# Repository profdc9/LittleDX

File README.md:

# LittleDX

New super cheap all-mode transceiver, details to come.

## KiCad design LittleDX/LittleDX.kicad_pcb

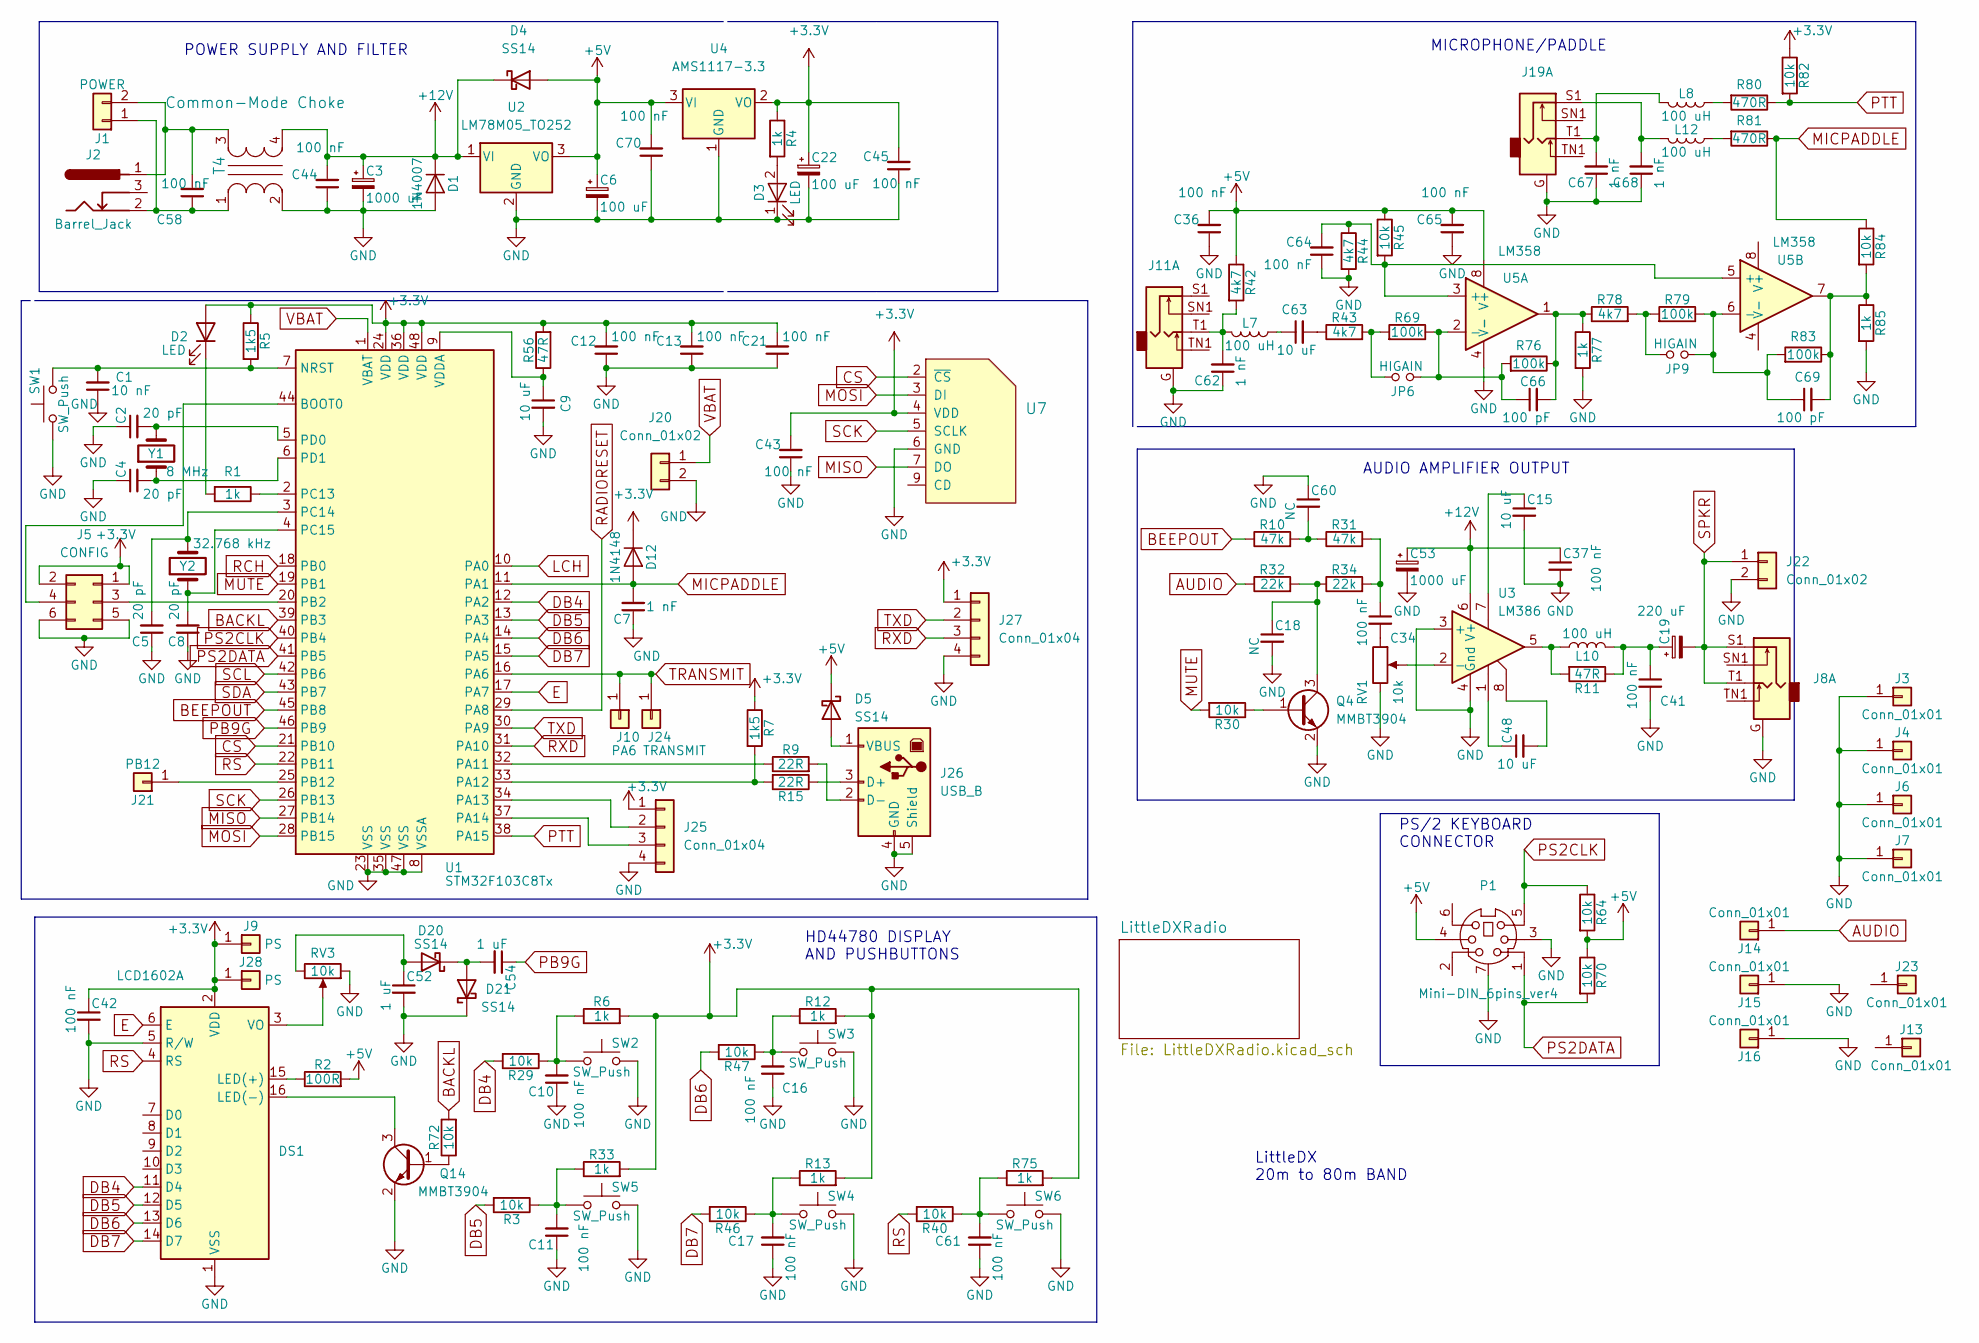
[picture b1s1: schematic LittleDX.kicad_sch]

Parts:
C1: 10 nF; C_0805_2012Metric_Pad1.18x1.45mm_HandSolder; LCSC C1710
C2, C4, C5, C8: 20 pF; C_0805_2012Metric_Pad1.18x1.45mm_HandSolder; LCSC C1804
C3, C53: 1000 uF; CP_Radial_D8.0mm_P3.50mm
C6: 100 uF; CP_Radial_D5.0mm_P2.50mm
C7, C62, C67, C68: 1 nF; C_0805_2012Metric_Pad1.18x1.45mm_HandSolder; LCSC C46653
C9, C15, C48, C63: 10 uF; C_0805_2012Metric_Pad1.18x1.45mm_HandSolder; LCSC C15850
C10, C11, C12, C13, C16, C17, C21, C36, C37, C41, C42, C43, C44, C45, C58, C61, C64, C65, C70: 100 nF; C_0805_2012Metric_Pad1.18x1.45mm_HandSolder; LCSC C49678
C18, C60: NC; C_0805_2012Metric_Pad1.18x1.45mm_HandSolder
C19: 220 uF; CP_Radial_D7.5mm_P2.50mm
C22: 100 uF; CP_Radial_D5.0mm_P2.00mm
C34: 100 nF; C_0805_2012Metric_Pad1.18x1.45mm_HandSolder
C52, C54: 1 uF; C_0805_2012Metric_Pad1.18x1.45mm_HandSolder; LCSC C28323
C66, C69: 100 pF; C_0805_2012Metric_Pad1.18x1.45mm_HandSolder; LCSC C1790
D1: 1N4007; D_DO-41_SOD81_P7.62mm_Horizontal
D2, D3: LED; LED_0805_2012Metric_Pad1.15x1.40mm_HandSolder; LCSC C2296
D4, D5, D20, D21: SS14; D_SMA_Handsoldering; LCSC C2480
D12: 1N4148; D_SOD-123; LCSC C81598
DS1: LCD1602A; WC1602A
J1: POWER; TerminalBlock_bornier-2_P5.08mm
J2: Barrel_Jack; BARREL_JACK
J3, J4, J6, J7, J13: Conn_01x01; 1pin
J5: CONFIG; PinHeader_2x03_P2.54mm_Vertical
J8, J11, J19: AudioJack2_Dual_Ground_Switch; PJ-3240-35mm-stereo
J9, J28: PS; PinHeader_1x01_P2.54mm_Vertical
J10: PA6; PinHeader_1x01_P2.54mm_Vertical
J14, J15, J16: Conn_01x01; Pin_Header_Straight_1x01_Pitch2.54mm
J20, J22: Conn_01x02; PinHeader_1x02_P2.54mm_Vertical
J21: PB12; PinHeader_1x01_P2.54mm_Vertical
J23: Conn_01x01; MountingHole_3.2mm_M3
J24: TRANSMIT; PinHeader_1x01_P2.54mm_Vertical
J25, J27: Conn_01x04; PinHeader_1x04_P2.54mm_Vertical
J26: USB_B; USB_B_OST_USB-B1HSxx_Horizontal
JP6, JP9: HIGAIN; PinHeader_1x02_P2.54mm_Vertical
L7, L8, L12: 100 uH; L_0805_2012Metric_Pad1.15x1.40mm_HandSolder; LCSC C68035
L10: 100 uH; L_Axial_L6.6mm_D2.7mm_P10.16mm_Horizontal_Vishay_IM-2
P1: Mini-DIN_6pins_ver4; Connector_Mini-DIN_Female_6Pin_2rows
Q4, Q14: MMBT3904; SOT-23; LCSC C20526
R1, R4, R6, R12, R13, R33, R75, R77, R85: 1k; R_0805_2012Metric_Pad1.20x1.40mm_HandSolder; LCSC C17513
R2: 100R; R_0805_2012Metric_Pad1.20x1.40mm_HandSolder; LCSC C17408
R3, R29, R30, R40, R45, R46, R47, R64, R70, R72, R82, R84: 10k; R_0805_2012Metric_Pad1.20x1.40mm_HandSolder; LCSC C17414
R5, R7: 1k5; R_0805_2012Metric_Pad1.20x1.40mm_HandSolder; LCSC C4310
R9, R15: 22R; R_0805_2012Metric_Pad1.20x1.40mm_HandSolder; LCSC C17561
R10, R31: 47k; R_0805_2012Metric_Pad1.20x1.40mm_HandSolder; LCSC C17713
R11, R56: 47R; R_0805_2012Metric_Pad1.20x1.40mm_HandSolder; LCSC C17714
R32, R34: 22k; R_0805_2012Metric_Pad1.20x1.40mm_HandSolder; LCSC C17560
R42, R43, R44, R78: 4k7; R_0805_2012Metric_Pad1.20x1.40mm_HandSolder; LCSC C17673
R69, R76, R79, R83: 100k; R_0805_2012Metric_Pad1.20x1.40mm_HandSolder; LCSC C149504
R80, R81: 470R; R_0805_2012Metric_Pad1.20x1.40mm_HandSolder; LCSC C17710
RV1: 10k; Potentiometer_Big_Small_Combined
RV3: 10k; Potentiometer_Triwood_RM-065
SW1, SW2, SW3, SW4, SW5, SW6: SW_Push; SW_PUSH_6mm
T4: Common-Mode Choke; DoubleWindingTransformer
U1: STM32F103C8Tx; LQFP-48_7x7mm_P0.5mm; LCSC C8304
U2: LM78M05_TO252; TO-252-2; LCSC C58069
U3: LM386; SOP-8_3.9x4.9mm_P1.27mm; LCSC C383071
U4: AMS1117-3.3; SOT-223-3_TabPin2; LCSC C6186
U5: LM358; SOP-8_3.9x4.9mm_P1.27mm; LCSC C7950
U7: MicroSD_SPI_CD; GCT-MEM2055-00-190-01-A; LCSC C2889257
Y1: 8 MHz; Crystal_SMD_5032-2Pin_5.0x3.2mm; LCSC C115962
Y2: 32.768 kHz; Crystal_SMD_3215-2Pin_3.2x1.5mm; LCSC C32346

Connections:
+3.3V: C12.2, C13.2, C21.2, C22.1, C42.1, C43.2, C45.2, D2.2 (A), D12.1 (K), DS1.2 (VDD), J5.1, J5.2, J9.1, J25.1, J27.1, J28.1, R4.1, R5.1, R6.2, R7.1, R12.2, R13.2, R33.2, R56.2, R75.2, R82.1, U1.24 (VDD), U1.36 (VDD), U1.48 (VDD), U4.2 (VO), U7.4 (VDD); also elsewhere on the board
+5V: C6.1, C36.2, C65.2, C70.2, D4.2 (A), D5.1 (K), P1.4, R2.2, R42.1, R45.1, R64.2, R70.1, U2.3 (VO), U4.3 (VI), U5.8 (V+); also elsewhere on the board
+12V: C3.1, C37.1, C44.2, C53.1, D1.1 (K), D4.1 (K), T4.4, U2.1 (VI), U3.6 (V+); also elsewhere on the board
AUDIO: J14.1, R32.1; also elsewhere on the board
BACKL: R72.2, U1.39 (PB3)
BEEPOUT: R10.1, U1.45 (PB8)
CS: U1.21 (PB10), U7.2 (~CS)
DB4: DS1.11 (D4), R29.2, U1.12 (PA2)
DB5: DS1.12 (D5), R3.2, U1.13 (PA3)
DB6: DS1.13 (D6), R47.2, U1.14 (PA4)
DB7: DS1.14 (D7), R46.2, U1.15 (PA5)
E: DS1.6 (E), U1.17 (PA7)
GND: C1.1, C2.1, C3.2, C4.1, C5.1, C6.2, C7.1, C8.1, C9.2, C10.1, C11.1, C12.1, C13.1, C15.2, C16.1, C17.1, C18.2, C21.1, C22.2, C36.1, C37.2, C41.2, C42.2, C43.1, C44.1, C45.1, C52.2, C53.2, C60.1, C61.1, C62.1, C64.1, C65.1, C67.1, C68.1, C70.1, D1.2 (A), D3.1 (K), D21.1 (K), DS1.1 (VSS), DS1.5 (R/W), J3.1, J4.1, J5.5, J5.6, J6.1, J7.1, J8.G, J11.G, J15.1, J16.1, J19.G, J20.2, J22.2, J25.4, J26.4 (GND), J26.5 (Shield), J27.4, P1.3, P1.7 (Shell), Q4.2 (E), Q14.2 (E), R44.2, R77.2, R85.2, RV1.3, RV3.1, SW1.1, SW2.2, SW3.2, SW4.2, SW5.2, SW6.2, T4.2, U1.8 (VSSA), U1.23 (VSS), U1.35 (VSS), U1.47 (VSS), U2.2 (GND), U3.3 (+), U3.4 (Gnd), U4.1 (GND), U5.4 (V-), U7.6 (GND); also elsewhere on the board
LCH: U1.10 (PA0); also elsewhere on the board
MICPADDLE: C7.2, D12.2 (A), R81.1, R84.1, U1.11 (PA1)
MISO: U1.27 (PB14), U7.7 (DO)
MOSI: U1.28 (PB15), U7.3 (DI)
MUTE: R30.2, U1.19 (PB1)
unnamed: C1.2, R5.2, SW1.2, U1.7 (NRST)
unnamed: C2.2, U1.5 (PD0), Y1.2
unnamed: C4.2, U1.6 (PD1), Y1.1
unnamed: C5.2, U1.3 (PC14), Y2.2
unnamed: C8.2, U1.4 (PC15), Y2.1
unnamed: C9.1, R56.1, U1.9 (VDDA)
unnamed: C10.2, R6.1, R29.1, SW2.1
unnamed: C11.2, R3.1, R33.1, SW5.1
unnamed: C15.1, U3.7
unnamed: C16.2, R12.1, R47.1, SW3.1
unnamed: C17.2, R13.1, R46.1, SW4.1
unnamed: C18.1, Q4.3 (C), R32.2, R34.1
unnamed: C19.1, C41.1, L10.2, R11.1
unnamed: C34.1, R31.2, R34.2
unnamed: C34.2, RV1.1
unnamed: C48.1, U3.1
unnamed: C48.2, U3.8
unnamed: C54.2, D20.1 (K), D21.2 (A)
unnamed: C58.1, J1.1, J2.2, T4.1
unnamed: C58.2, J1.2, J2.1, T4.3
unnamed: C60.2, R10.2, R31.1
unnamed: C61.2, R40.1, R75.1, SW6.1
unnamed: C62.2, J11.T1, L7.2, R42.2
unnamed: C63.1, L7.1
unnamed: C63.2, R43.1
unnamed: C64.2, R44.1, R45.2, U5.3 (+), U5.5 (+)
unnamed: C66.1, JP6.1, R69.1, R76.2, U5.2 (-)
unnamed: C66.2, R76.1, R77.1, R78.1, U5.1
unnamed: C67.2, J19.T1, L8.2
unnamed: C68.2, J19.S1, L12.2
unnamed: C69.1, JP9.1, R79.1, R83.2, U5.6 (-)
unnamed: C69.2, R83.1, R84.2, R85.1, U5.7
unnamed: D2.1 (K), R1.2
unnamed: D3.2 (A), R4.2
unnamed: D5.2 (A), J26.1 (VBUS)
unnamed: DS1.3 (VO), RV3.2
unnamed: DS1.15 (LED(+)), R2.1
unnamed: DS1.16 (LED(-)), Q14.3 (C)
unnamed: J5.3, U1.20 (PB2)
unnamed: J5.4, U1.44 (BOOT0)
unnamed: J21.1, U1.25 (PB12)
unnamed: J25.2, U1.34 (PA13)
unnamed: J25.3, U1.37 (PA14)
unnamed: J26.2 (D-), R9.2
unnamed: J26.3 (D+), R15.1
unnamed: JP6.2, R43.2, R69.2
unnamed: JP9.2, R78.2, R79.2
unnamed: L8.1, R80.2
unnamed: L10.1, R11.2, U3.5
unnamed: L12.1, R81.2
unnamed: Q4.1 (B), R30.1
unnamed: Q14.1 (B), R72.1
unnamed: R1.1, U1.2 (PC13)
unnamed: R9.1, U1.32 (PA11)
unnamed: R7.2, R15.2, U1.33 (PA12)
unnamed: RV1.2, U3.2 (-)
unnamed: C52.1, D20.2 (A), RV3.3
PB9G: C54.1, U1.46 (PB9)
PS2CLK: P1.5, R64.1, U1.40 (PB4)
PS2DATA: P1.1, R70.2, U1.41 (PB5)
PTT: R80.1, R82.2, U1.38 (PA15)
RADIORESET: U1.29 (PA8); also elsewhere on the board
RCH: U1.18 (PB0); also elsewhere on the board
RS: DS1.4 (RS), R40.2, U1.22 (PB11)
RXD: J27.3, U1.31 (PA10)
SCK: U1.26 (PB13), U7.5 (SCLK)
SCL: U1.42 (PB6); also elsewhere on the board
SDA: U1.43 (PB7); also elsewhere on the board
SPKR: C19.2, J8.S1, J8.T1, J22.1
TRANSMIT: J10.1, J24.1, U1.16 (PA6); also elsewhere on the board
TXD: J27.2, U1.30 (PA9)
VBAT: J20.1, U1.1 (VBAT)

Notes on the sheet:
POWER SUPPLY AND FILTER
PS/2 KEYBOARD CONNECTOR
MICROPHONE/PADDLE
AUDIO AMPLIFIER OUTPUT
LittleDX 20m to 80m BAND
HD44780 DISPLAY AND PUSHBUTTONS

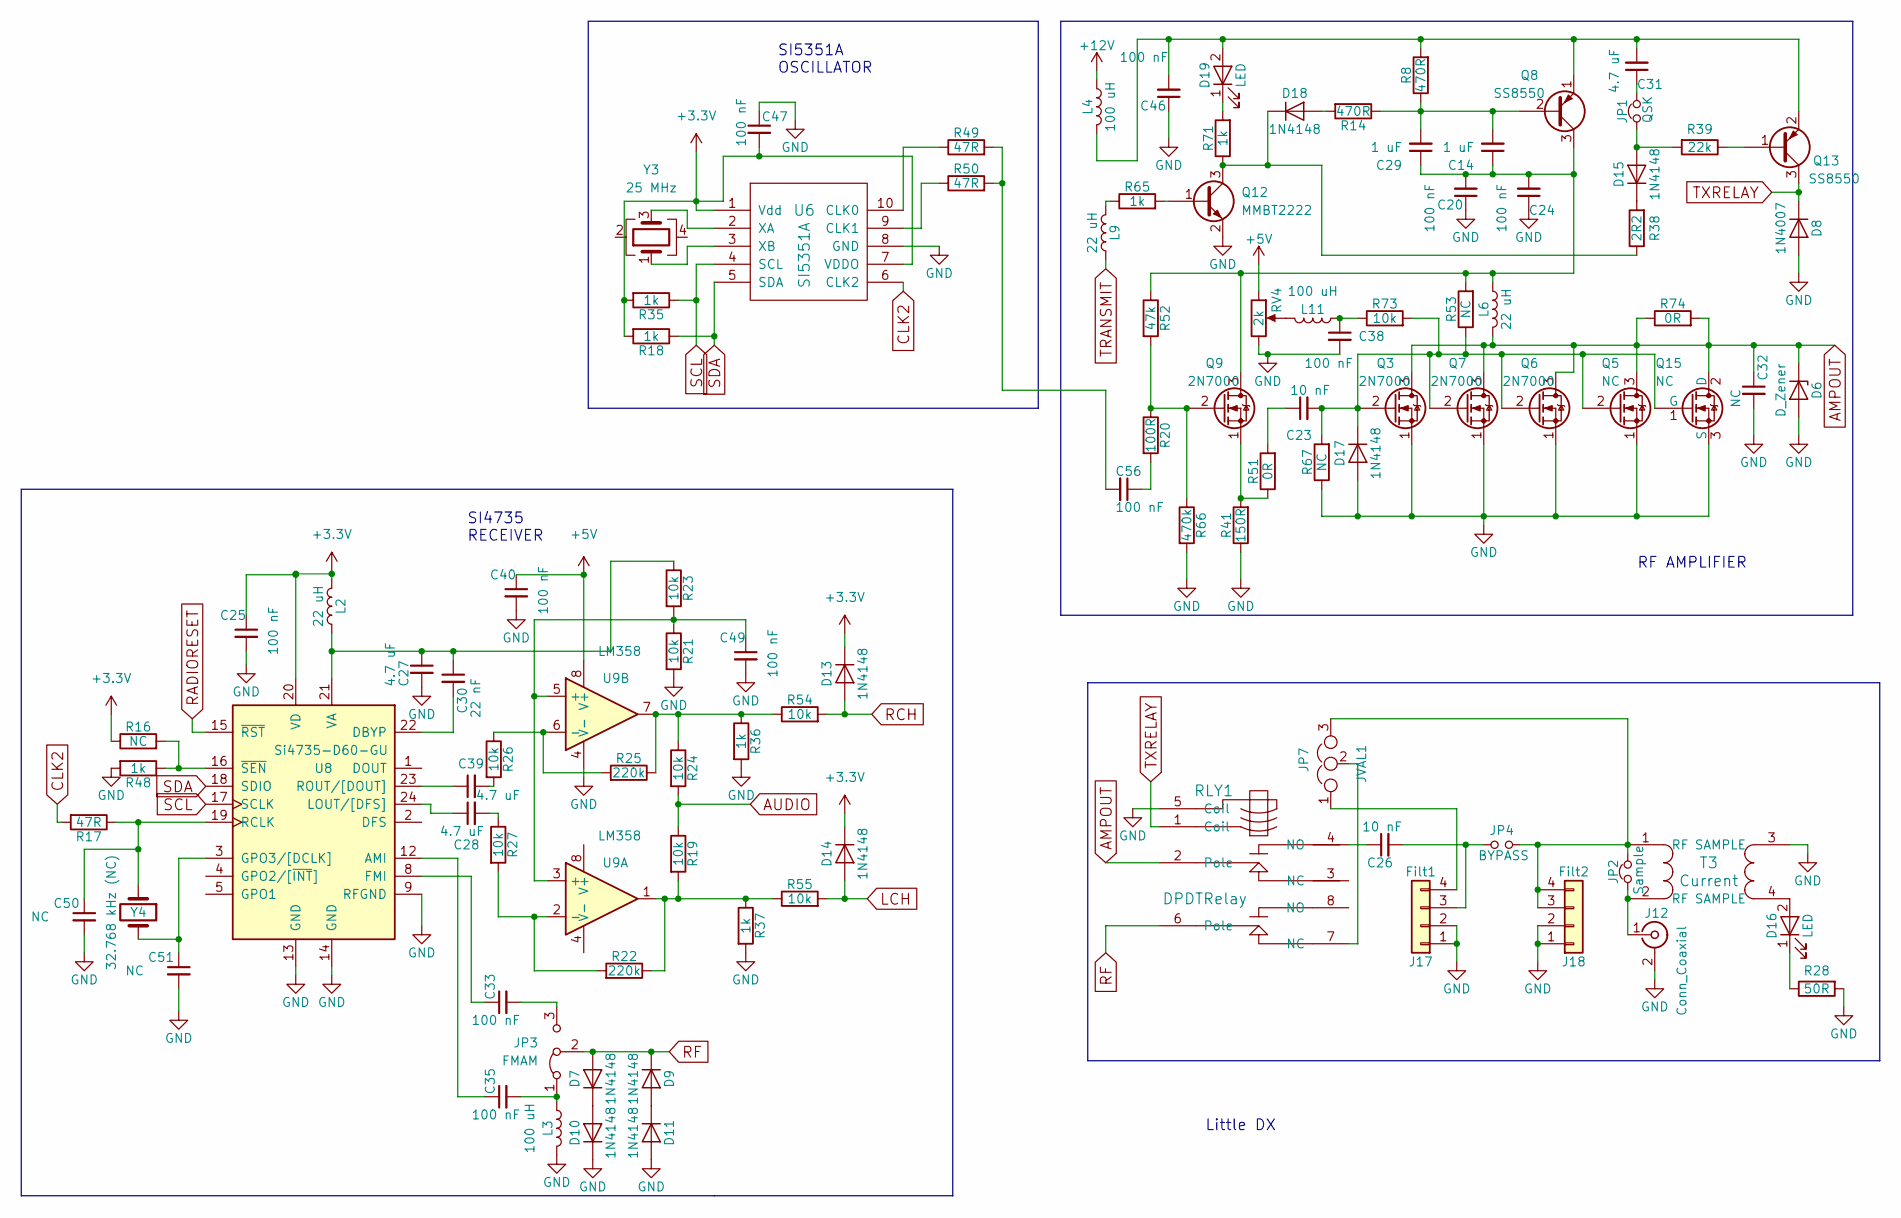
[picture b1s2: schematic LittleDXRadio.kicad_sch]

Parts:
C14, C29: 1 uF; C_0805_2012Metric_Pad1.18x1.45mm_HandSolder; LCSC C28323
C20, C24, C25, C33, C35, C38, C40, C46, C47, C49, C56: 100 nF; C_0805_2012Metric_Pad1.18x1.45mm_HandSolder; LCSC C49678
C23, C26: 10 nF; C_0805_2012Metric_Pad1.18x1.45mm_HandSolder; LCSC C1710
C27, C28, C31, C39: 4.7 uF; C_0805_2012Metric_Pad1.18x1.45mm_HandSolder; LCSC C1779
C30: 22 nF; C_0805_2012Metric_Pad1.18x1.45mm_HandSolder; LCSC C1729
C32, C50, C51: NC; C_0805_2012Metric_Pad1.18x1.45mm_HandSolder
D6: D_Zener; D_DO-41_SOD81_P7.62mm_Horizontal
D7, D9, D10, D11, D13, D14, D15, D17, D18: 1N4148; D_SOD-123; LCSC C81598
D8: 1N4007; D_SMA_Handsoldering; LCSC C95872
D16, D19: LED; LED_0805_2012Metric_Pad1.15x1.40mm_HandSolder; LCSC C2296
J12: Conn_Coaxial; bnc_90_1-1337543-0_pad_combo
J17: Filt1; Pin_Header_Straight_1x04_Pitch2.54mm
J18: Filt2; Pin_Header_Straight_1x04_Pitch2.54mm
JP1: QSK; Pin_Header_Straight_1x02_Pitch2.54mm
JP2: Sample; Pin_Header_Straight_1x02_Pitch2.54mm
JP3: FMAM; PinHeader_1x03_P2.54mm_Vertical
JP4: BYPASS; Pin_Header_Straight_1x02_Pitch2.54mm
JP7: JVAL1; Pin_Header_Straight_1x03_Pitch2.54mm
L2, L9: 22 uH; L_0805_2012Metric_Pad1.15x1.40mm_HandSolder; LCSC C32375
L3, L11: 100 uH; L_0805_2012Metric_Pad1.15x1.40mm_HandSolder; LCSC C68035
L4: 100 uH; SmallVerticalToroid
L6: 22 uH; SmallVerticalToroid
Q3, Q6, Q7, Q9: 2N7000; TO-92_Inline_Wide
Q5: NC; TO-92_Inline_Wide
Q8: SS8550; TO-92_Inline_Wide
Q12: MMBT2222; SOT-23; LCSC C8512
Q13: SS8550; SOT-23; LCSC C8542
Q15: NC; TO-220-3_Vertical
R8, R14: 470R; R_0805_2012Metric_Pad1.20x1.40mm_HandSolder; LCSC C17710
R16, R53, R67: NC; R_0805_2012Metric_Pad1.20x1.40mm_HandSolder
R17, R49, R50: 47R; R_0805_2012Metric_Pad1.20x1.40mm_HandSolder; LCSC C17714
R18, R35, R36, R37, R48, R65, R71: 1k; R_0805_2012Metric_Pad1.20x1.40mm_HandSolder; LCSC C17513
R19, R21, R23, R24, R26, R27, R54, R55, R73: 10k; R_0805_2012Metric_Pad1.20x1.40mm_HandSolder; LCSC C17414
R20: 100R; R_0805_2012Metric_Pad1.20x1.40mm_HandSolder; LCSC C17408
R22, R25: 220k; R_0805_2012Metric_Pad1.20x1.40mm_HandSolder; LCSC C17556
R28: 50R; R_0805_2012Metric_Pad1.20x1.40mm_HandSolder; LCSC C17720
R38: 2R2; R_0805_2012Metric_Pad1.20x1.40mm_HandSolder; LCSC C17521
R39: 22k; R_0805_2012Metric_Pad1.20x1.40mm_HandSolder; LCSC C17560
R41: 150R; R_Axial_DIN0309_L9.0mm_D3.2mm_P12.70mm_Horizontal
R51, R74: 0R; R_0805_2012Metric_Pad1.20x1.40mm_HandSolder; LCSC C17477
R52: 47k; R_0805_2012Metric_Pad1.20x1.40mm_HandSolder; LCSC C17713
R66: 470k; R_0805_2012Metric_Pad1.20x1.40mm_HandSolder; LCSC C17709
RLY1: DPDTRelay; G2VRelay
RV4: 2k; Potentiometer_Trimmer_Bourns_3296W
T3: Current; SamplingTransformer
U6: SI5351A; MSOP-10_3x3mm_Pitch0.5mm; LCSC C5451727
U8: Si4735-D60-GU; SSOP-24_3.9x8.7mm_P0.635mm; LCSC C1526089
U9: LM358; SOP-8_3.9x4.9mm_P1.27mm; LCSC C7950
Y3: 25 MHz; Crystal_SMD_3225-4Pin_3.2x2.5mm_HandSoldering; LCSC C9006
Y4: 32.768 kHz (NC); Crystal_SMD_3215-2Pin_3.2x1.5mm

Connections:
+3.3V: C25.1, C47.2, D13.1 (K), D14.1 (K), L2.2, R16.1, R18.2, R35.2, U6.1 (Vdd), U6.7 (VDDO), U8.20 (VD); also elsewhere on the board
+5V: C40.1, RV4.1, U9.8 (V+); also elsewhere on the board
+12V: L4.1; also elsewhere on the board
AMPOUT: C32.1, D6.1 (K), L6.2, Q3.3 (D), Q5.3 (D), Q6.3 (D), Q7.3 (D), Q15.2 (D), R74.1, R74.2, RLY1.2 (Pole)
AUDIO: R19.1, R24.2; also elsewhere on the board
CLK2: R17.2, U6.6 (CLK2)
GND: C20.1, C24.1, C25.2, C27.2, C32.2, C38.2, C40.2, C46.1, C47.1, C49.2, C50.2, C51.2, D6.2 (A), D8.2 (A), D10.1 (K), D11.2 (A), D17.2 (A), J12.2 (Ext), J17.1, J17.2, J18.1, J18.2, L3.2, Q3.1 (S), Q5.1 (S), Q6.1 (S), Q7.1 (S), Q12.2 (E), Q15.3 (S), R21.2, R28.2, R36.2, R37.2, R41.1, R48.2, R66.2, R67.1, RLY1.5 (Coil), RV4.3, T3.3 (SAMPLE), U6.8 (GND), U8.9 (RFGND), U8.13 (GND), U8.14 (GND), U9.4 (V-); also elsewhere on the board
LCH: D14.2 (A), R55.2; also elsewhere on the board
unnamed: C14.1, C20.2, C24.2, C29.1, L6.1, Q8.3 (C), Q9.3 (D), R52.1, R53.2
unnamed: C14.2, C29.2, Q8.2 (B), R8.1, R14.1
unnamed: C23.1, R51.2
unnamed: C23.2, D17.1 (K), Q3.2 (G), Q5.2 (G), Q6.2 (G), Q7.2 (G), Q15.1 (G), R53.1, R67.2, R73.2
unnamed: C26.1, RLY1.4 (NO)
unnamed: C26.2, J17.3, JP4.1
unnamed: C27.1, C30.1, L2.1, R23.1, U8.21 (VA)
unnamed: C28.1, U8.24 (LOUT/[DFS])
unnamed: C28.2, R27.1
unnamed: C30.2, U8.22 (DBYP)
unnamed: C31.1, JP1.2
unnamed: C31.2, C46.2, D19.2 (A), L4.2, Q8.1 (E), Q13.2 (E), R8.2
unnamed: C33.1, U8.8 (FMI)
unnamed: C33.2, JP3.3 (B)
unnamed: C35.1, U8.12 (AMI)
unnamed: C35.2, JP3.1 (A), L3.1
unnamed: C38.1, L11.1, R73.1
unnamed: C39.1, U8.23 (ROUT/[DOUT])
unnamed: C39.2, R26.2
unnamed: C49.1, R21.1, R23.2, U9.3 (+), U9.5 (+)
unnamed: C50.1, R17.1, U8.19 (RCLK), Y4.1
unnamed: C51.1, U8.3 (GPO3/[DCLK]), Y4.2
unnamed: C56.1, R20.2
unnamed: C56.2, R49.2, R50.2
unnamed: D7.1 (K), D10.2 (A)
unnamed: D9.2 (A), D11.1 (K)
unnamed: D15.1 (K), R38.2
unnamed: D15.2 (A), JP1.1, R39.2
unnamed: D16.1 (K), R28.1
unnamed: D16.2 (A), T3.4 (SAMPLE)
unnamed: D18.1 (K), Q12.3 (C), R38.1, R71.1
unnamed: D18.2 (A), R14.2
unnamed: D19.1 (K), R71.2
unnamed: J12.1 (In), JP2.1, T3.2 (RF)
unnamed: J17.4, JP7.1
unnamed: J18.3, J18.4, JP2.2, JP4.2, JP7.3, T3.1 (RF)
unnamed: JP7.2, RLY1.7 (NC)
unnamed: L9.2, R65.1
unnamed: L11.2, RV4.2
unnamed: Q9.1 (S), R41.2, R51.1
unnamed: Q9.2 (G), R20.1, R52.2, R66.1
unnamed: Q12.1 (B), R65.2
unnamed: Q13.1 (B), R39.1
unnamed: R16.2, R48.1, U8.16 (~SEN)
unnamed: R19.2, R22.1, R37.1, R55.1, U9.1
unnamed: R22.2, R27.2, U9.2 (-)
unnamed: R24.1, R25.1, R36.1, R54.1, U9.7
unnamed: R25.2, R26.1, U9.6 (-)
unnamed: R49.1, U6.10 (CLK0)
unnamed: R50.1, U6.9 (CLK1)
unnamed: U6.2 (XA), Y3.3
unnamed: U6.3 (XB), Y3.1
RADIORESET: U8.15 (~RST); also elsewhere on the board
RCH: D13.2 (A), R54.2; also elsewhere on the board
RF: D7.2 (A), D9.1 (K), JP3.2 (C), RLY1.6 (Pole)
SCL: R35.1, U6.4 (SCL), U8.17 (SCLK); also elsewhere on the board
SDA: R18.1, U6.5 (SDA), U8.18 (SDIO); also elsewhere on the board
TRANSMIT: L9.1; also elsewhere on the board
TXRELAY: D8.1 (K), Q13.3 (C), RLY1.1 (Coil)

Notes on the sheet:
SI4735 RECEIVER
Little DX
SI5351A OSCILLATOR
RF AMPLIFIER

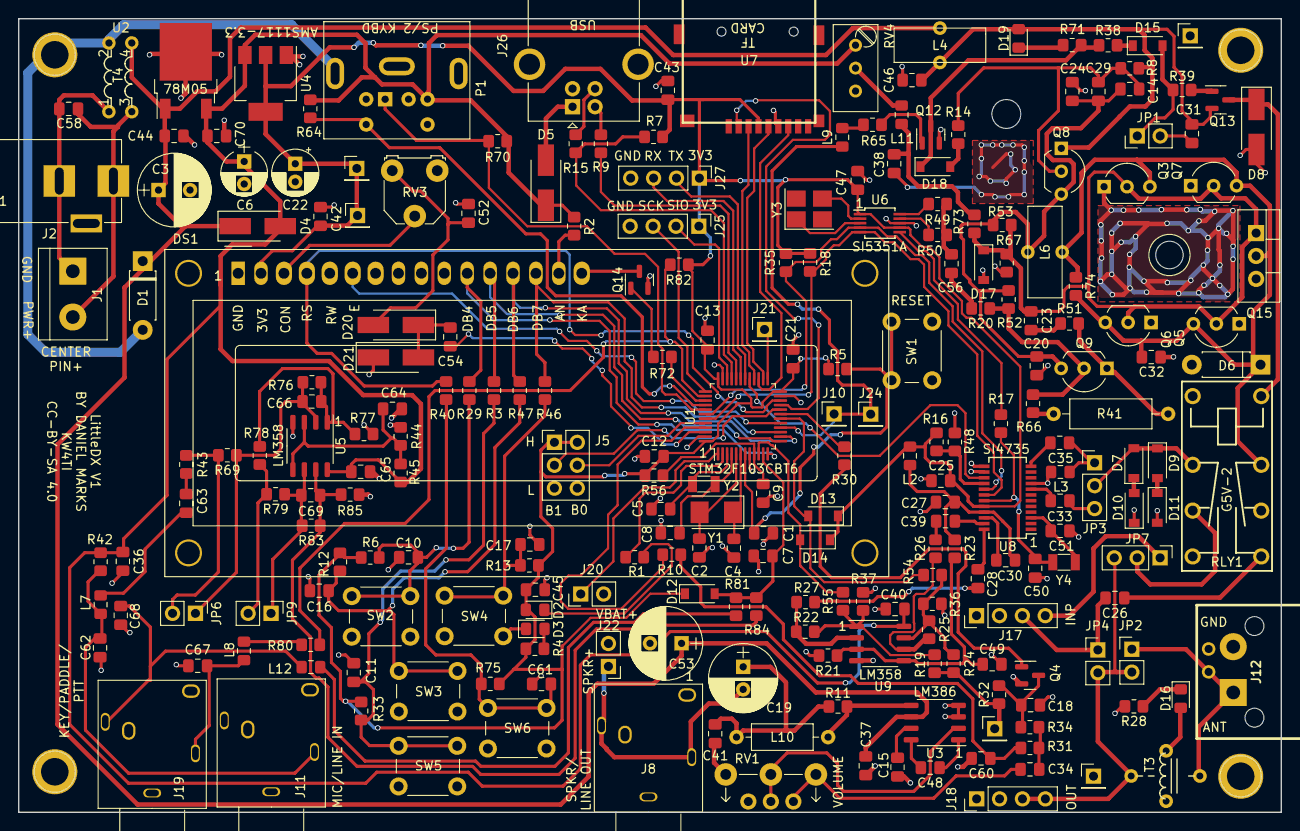
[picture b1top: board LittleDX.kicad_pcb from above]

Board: 2 copper layers, 140.0 x 88.0 mm, 248 parts (0 on the bottom side), 146 nets.

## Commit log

2023-06-17 Small moving around of components
2023-07-07 JLCPCB version 2
2023-07-08 Revised JLCPCB order: added negative LCD voltage supply

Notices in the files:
LittleDX/LittleDX.kicad_pcb:
CC-BY-SA 4.0
